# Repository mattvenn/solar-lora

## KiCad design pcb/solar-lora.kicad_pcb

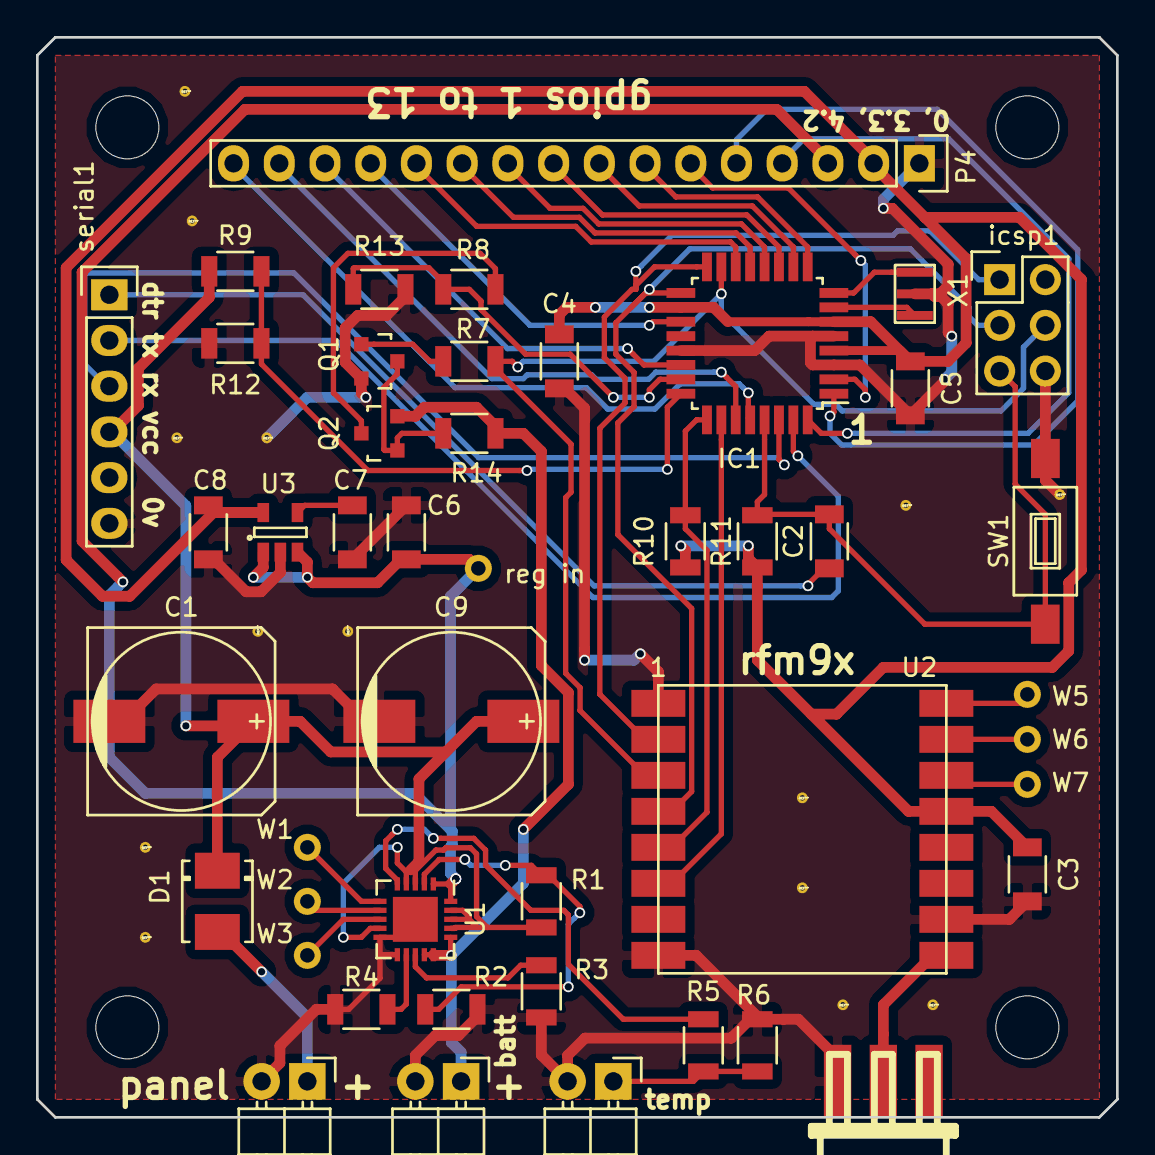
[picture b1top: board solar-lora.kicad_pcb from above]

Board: 2 copper layers, 60.0 x 60.0 mm, 46 parts (0 on the bottom side), 48 nets.

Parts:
C1, C9: 2000u; c_elec_10x10
C2: 100n; C_1206
C3: 10u; C_1206
C4, C8: 2.2u; C_1206
C5, C6: 1u; C_1206
C7: 0.01u; C_1206
D1: D_Schottky; DO-214BA
IC1: ATMEGA328P-A; TQFP-32_7x7mm_Pitch0.8mm
P1: panel; Pin_Header_Angled_1x02
P2: lipo; Pin_Header_Angled_1x02
P3: therm; Pin_Header_Angled_1x02
P4: CONN_01X16; Pin_Header_Straight_1x16
P5: BNC; CON-SMA-EDGE
Q1: BC849; SOT-23
Q2: Q_PMOS_GSD; SOT-23
R1: 270k; R_1206
R2, R4: 100k; R_1206
R3, R5, R6: 2k; R_1206
R7, R12, R13, R14: 10k; R_1206
R8, R9: 4.7k; R_1206
R10, R11: 20k; R_1206
SW1: SW_PUSH; SW_SPST_FSMSM
U1: mcp73871; QFN-20-1EP_4x4mm_Pitch0.5mm
U2: rfm9x; rf9x
U3: LP2985-33DBVR; SOT-23-5
W1, W2, W3, W5, W6, W7: TEST_1P; Measurement_Point_Round-TH_Small
X1: CRYSTAL_SMD; cstce-v
icsp1: icsp; Pin_Header_Straight_2x03
reg in: TEST_1P; Measurement_Point_Round-TH_Small
serial1: serial; Pin_Header_Straight_1x06

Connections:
+3V3: C3.1, C4.2, C5.1, C8.1, IC1.4, IC1.6, IC1.18, P4.2, R10.1, R11.1, U2.13, U3.5
/stat1: U1.8, W3.1
/stat2: U1.7, W2.1
Earth: C1.2, C3.2, C4.1, C5.2, C6.2, C7.2, C8.2, C9.2, IC1.3, IC1.5, IC1.21, P1.2, P2.2, P3.2, P4.1, P5.2, Q1.2, R2.2, R3.1, R4.1, R6.1, R12.2, R13.2, SW1.2, U1.10, U1.11, U1.21, U2.1, U2.8, U2.10, U3.2, X1.3, icsp1.6, serial1.6
unnamed: C2.1, serial1.1
unnamed: C7.1, U3.4
unnamed: D1.2, P1.1
unnamed: IC1.7, X1.1
unnamed: IC1.8, X1.2
unnamed: P3.1, R5.1, R6.2
unnamed: P5.1, U2.9
unnamed: Q1.1, R7.1
unnamed: Q1.3, Q2.1, R14.1
unnamed: Q2.3, R8.1
unnamed: R1.2, R2.1, U1.2
unnamed: R3.2, U1.13
unnamed: R4.2, U1.12
unnamed: R5.2, U1.5
unnamed: U1.6, W1.1
unnamed: U2.14, W7.1
unnamed: U2.15, W6.1
unnamed: U2.16, W5.1
VCC: C1.1, C9.1, D1.1, R1.1, R9.1, U1.3, U1.4, U1.9, U1.17, U1.18, U1.19, serial1.4
batt: P2.1, Q2.2, R14.2, U1.14, U1.15, U1.16
batt-adc: IC1.23, R8.2, R13.1
divider: IC1.15, R7.2, U2.3, icsp1.4
gpio1: IC1.32, P4.4
gpio2: IC1.1, P4.5
gpio3: IC1.2, P4.6
gpio4: IC1.9, P4.7
gpio5: IC1.10, P4.8
gpio6: IC1.11, P4.9
gpio7: IC1.12, P4.10
gpio8: IC1.13, P4.11
gpio9: IC1.14, P4.12
gpio10: IC1.19, P4.13
gpio11: IC1.22, P4.14
gpio12: IC1.27, P4.15
gpio13: IC1.28, P4.16
miso: IC1.16, U2.2, icsp1.1
panel: IC1.24, R9.2, R12.1
radio_cs: IC1.25, R10.2, U2.5
reg_in: C6.1, P4.3, U1.1, U1.20, U3.1, U3.3, reg in.1
reset: C2.2, IC1.29, R11.2, SW1.1, icsp1.5
rfm-reset: IC1.26, U2.6
rx: IC1.30, serial1.3
sck: IC1.17, U2.4, icsp1.3
tx: IC1.31, serial1.2

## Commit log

2017-01-20 Link to adafruit analysis of lipo charger
2017-01-20 schematic checked and first layout
2017-01-31 sent to fab and resistor calcs for charger
2017-02-07 working test sending panel and battery voltage
2017-02-07 posts lora data to phant
2017-02-18 post RSSI
2017-02-18 packet count
2017-02-18 added dash
2017-02-18 platformio
